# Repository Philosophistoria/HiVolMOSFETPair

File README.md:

View this project on [CADLAB.io](https://cadlab.io/project/1965). 

# HiVolMOSFETPair

Test circuit of Hi-Voltage N/P MOS FET switching

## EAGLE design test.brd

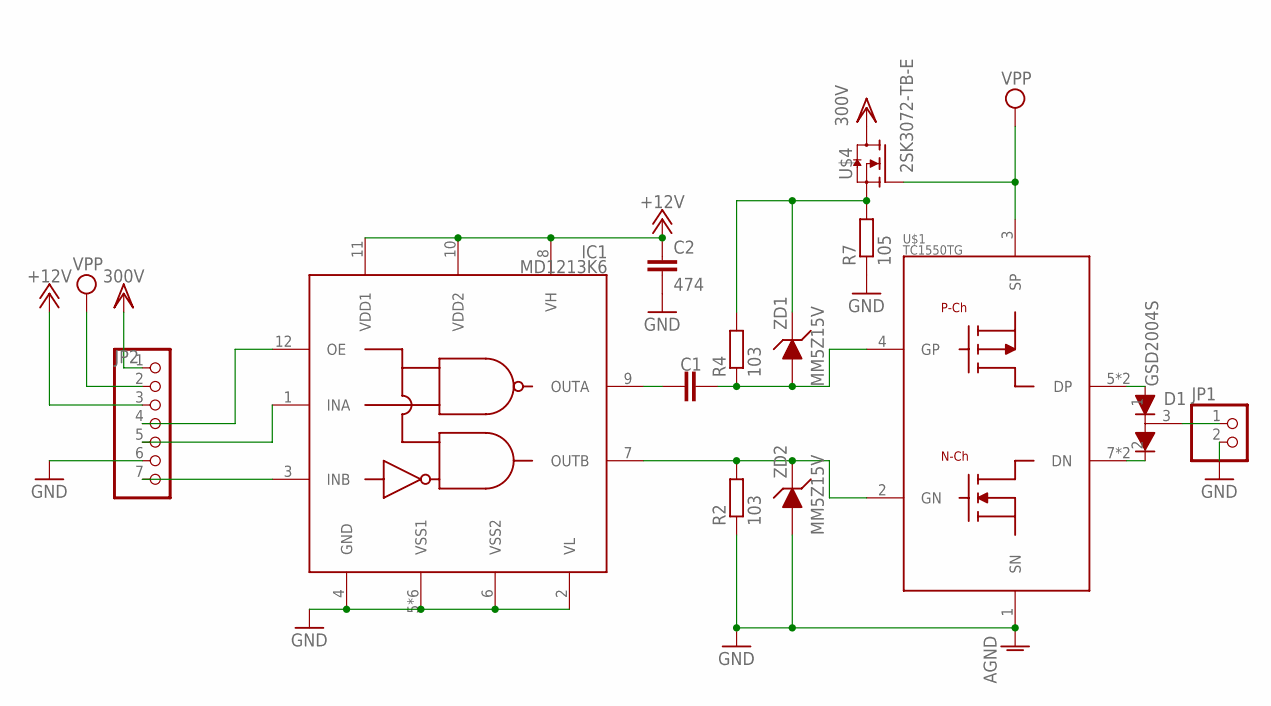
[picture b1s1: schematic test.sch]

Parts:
C1: C-EUC3216; C3216
C2: 474; C025-024X044
D1: GSD2004S; SOT23
IC1: MD1213K6; QFN12
JP1: PINHD-1X2; 1X02
JP2: PINHD-1X7; 1X07
R2, R4: 103; 0204/5
R7: 105; 0204/5
U$1: TC1550TG; SOIC-08LG
U$4: 2SK3072-TB-E; SOT95P250X120-3
ZD1, ZD2: MM5Z15V; SOD523

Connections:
+12V: C2.1, IC1.8 (VH), IC1.10 (VDD2), IC1.11 (VDD1), JP2.3
GND: C2.2, IC1.2 (VL), IC1.4 (GND), IC1.5 (VSS1), IC1.6 (VSS2), IC1.THP (VSS1), IC1.THV$1 (VSS1), IC1.THV$2 (VSS1), IC1.THV$3 (VSS1), IC1.THV$4 (VSS1), JP1.2, JP2.6, R2.1, R7.1, U$1.1 (SN), ZD2.P$2
unnamed: IC1.7 (OUTB), R2.2, U$1.2 (GN), ZD2.P$1 (K)
unnamed: C1.1, IC1.9 (OUTA)
unnamed: C1.2, R4.1, U$1.4 (GP), ZD1.P$2
unnamed: IC1.1 (INA), JP2.5
unnamed: IC1.12 (OE), JP2.4
unnamed: R4.2, R7.2, U$4.2 (S), ZD1.P$1 (K)
unnamed: D1.1, U$1.5 (DP), U$1.6 (DP)
unnamed: D1.2, U$1.7 (DN), U$1.8 (DN)
unnamed: D1.3, JP1.1
unnamed: IC1.3 (INB), JP2.7
VDD: JP2.1, U$4.3 (D)
VPP: JP2.2, U$1.3 (SP), U$4.1 (G)

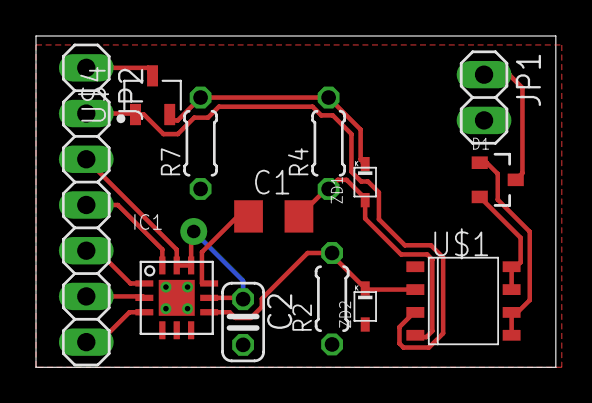
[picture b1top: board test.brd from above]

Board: 2 copper layers, 28.9 x 18.4 mm, 13 parts (0 on the bottom side), 14 nets.

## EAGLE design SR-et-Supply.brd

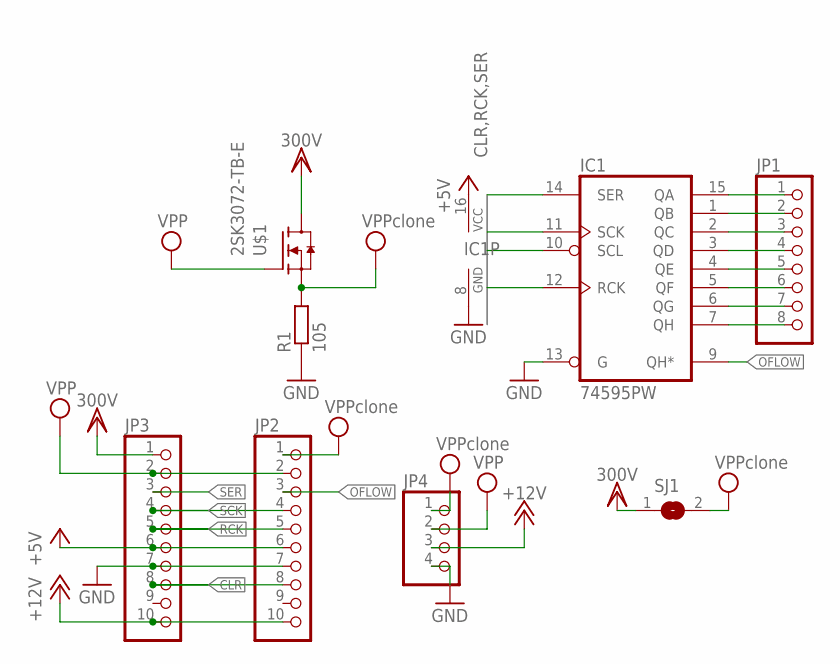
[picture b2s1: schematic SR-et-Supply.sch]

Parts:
IC1: 74595PW; TTSOP16
JP1: PINHD-1X8; 1X08
JP2, JP3: PINHD-1X10; 1X10
JP4: PINHD-1X4; 1X04
R1: 105; 0204/5
SJ1: SJ
U$1: 2SK3072-TB-E; SOT95P250X120-3

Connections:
300V: JP3.1, SJ1.1, U$1.3 (D)
+5V: IC1.16 (VCC), JP2.6, JP3.6
+12V: JP2.10, JP3.10, JP4.3
CLR: IC1.10 (SCL), JP2.8, JP3.8
GND: IC1.8 (GND), IC1.13 (G), JP2.7, JP3.7, JP4.4, R1.1
unnamed: IC1.15 (QA), JP1.1
unnamed: IC1.1 (QB), JP1.2
unnamed: IC1.2 (QC), JP1.3
unnamed: IC1.3 (QD), JP1.4
unnamed: IC1.4 (QE), JP1.5
unnamed: IC1.5 (QF), JP1.6
unnamed: IC1.6 (QG), JP1.7
unnamed: IC1.7 (QH), JP1.8
OFLOW: IC1.9 (QH*), JP2.3
RCK: IC1.12 (RCK), JP2.5, JP3.5
SCK: IC1.11 (SCK), JP2.4, JP3.4
SER: IC1.14 (SER), JP3.3
VPP: JP2.2, JP3.2, JP4.2, U$1.1 (G)
VPPCLONE: JP2.1, JP4.1, R1.2, SJ1.2, U$1.2 (S)

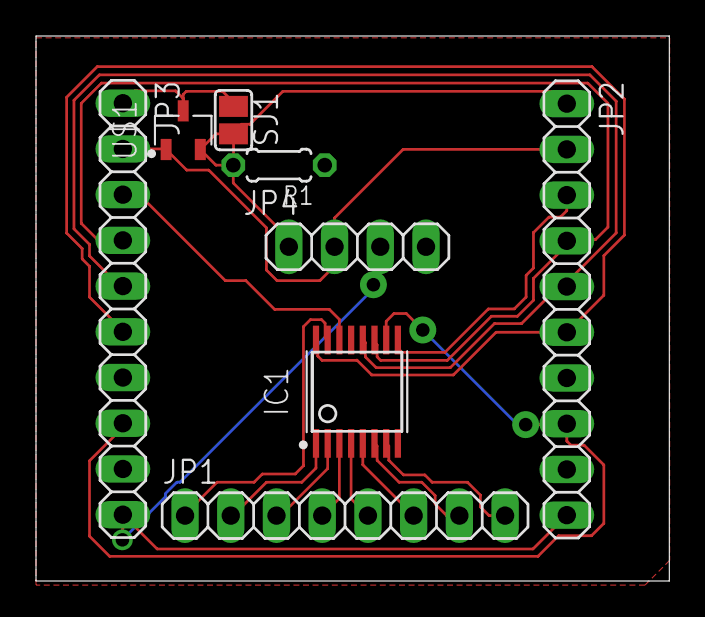
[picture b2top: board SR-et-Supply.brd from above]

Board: 2 copper layers, 35.2 x 30.3 mm, 8 parts (0 on the bottom side), 19 nets.

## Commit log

2019-07-06 Backlink to CADLAB.io has been added.
2019-07-06 added a NPN for like voltage follower
2019-07-08 rearranged devices
2019-07-10 replace the transistor with FET which compose a source follower.*
2019-07-16 replaced FETs for switching with cheaper lower breakdown voltage ones; and a added high voltage capacitor
2019-07-17 replace lower voltage FET by CMOS for putting off a CR circuit between HiVol-PMOS-Gate and 12V source.
2019-07-17 removed source follower FET, which will be added on another board
2019-07-19 rearrainged devies and added a solder junction
2019-07-19 Make Source Follwer FET derived from the existing test board to SR-et-Supply, and added ShiftResistor to it
2019-07-19 added cmos designed fet driver
2019-08-31 modified a value of 300V source symbol; Having a ploblem probably caused by Capacitor which require 240ms to charge
